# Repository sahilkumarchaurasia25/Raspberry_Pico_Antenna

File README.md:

# Raspberry_Pico_Antenna

You can refer the code from github repository by AndyRids, https://github.com/AndyRids/pico-nrf24 
Front view

Back View

Pcb design

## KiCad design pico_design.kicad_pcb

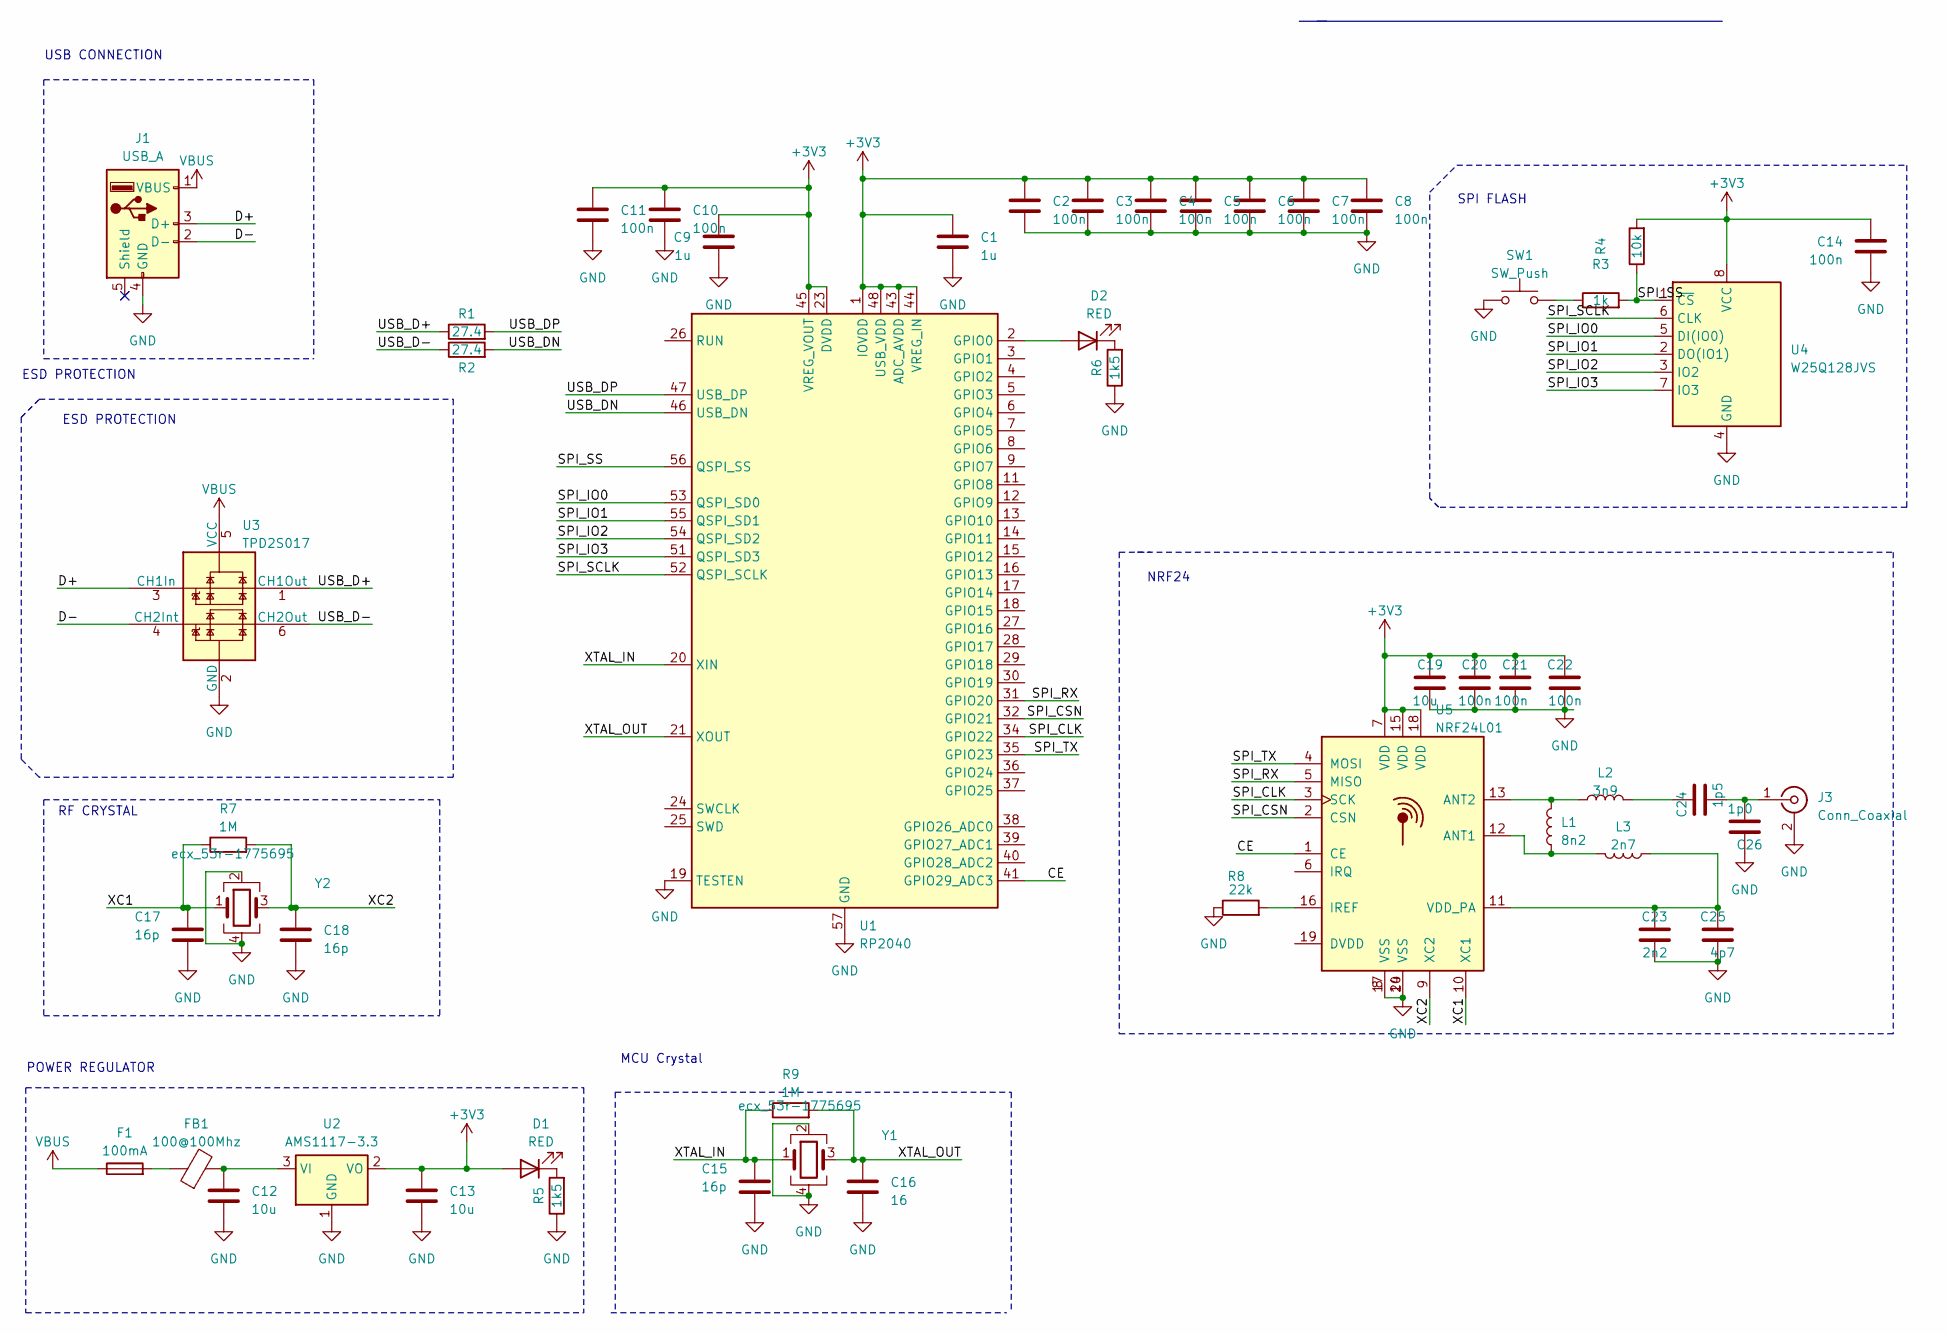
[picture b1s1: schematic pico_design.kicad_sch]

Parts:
C1, C9: 1u; C_0805_2012Metric
C2, C3, C4, C5, C6, C7, C8, C10, C11, C14, C20, C21, C22: 100n; C_0402_1005Metric
C12, C13, C19: 10u; C_0805_2012Metric
C15, C17, C18: 16p; C_0402_1005Metric
C16: 16; C_0402_1005Metric
C23: 2n2; C_0402_1005Metric
C24: 1p5; C_0402_1005Metric
C25: 4p7; C_0402_1005Metric
C26: 1p0; C_0402_1005Metric
D1, D2: RED; LED_0402_1005Metric
F1: 100mA; Fuse_0805_2012Metric
FB1: 100@100Mhz; C_0805_2012Metric
J1: USB_A; USB_A_CNCTech_1001-011-01101_Horizontal
J3: Conn_Coaxial; SMA_Samtec_SMA-J-P-X-ST-EM1_EdgeMount
L1: 8n2; L_0402_1005Metric
L2: 3n9; L_0402_1005Metric
L3: 2n7; L_0402_1005Metric
R1, R2: 27.4; R_0402_1005Metric
R3: 1k; R_0402_1005Metric
R4: 10k; R_0402_1005Metric
R5, R6: 1k5; R_0402_1005Metric
R7, R9: 1M; R_0402_1005Metric
R8: 22k; R_0402_1005Metric
SW1: SW_Push; SW_SPST_B3U-1000P
U1: RP2040; QFN-56-1EP_7x7mm_P0.4mm_EP3.2x3.2mm
U2: AMS1117-3.3; SOT-223-3_TabPin2
U3: TPD2S017; SOT-23-6
U4: W25Q128JVS; SOIC-8_5.23x5.23mm_P1.27mm
U5: NRF24L01; QFN-20-1EP_4x4mm_P0.5mm_EP2.5x2.5mm
Y1, Y2: ecx_53r-1775695; Crystal_SMD_SeikoEpson_TSX3225-4Pin_3.2x2.5mm

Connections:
+3V3: C1.1, C2.1, C3.1, C4.1, C5.1, C6.1, C7.1, C8.1, C9.1, C10.1, C11.1, C13.1, C14.1, C19.1, C20.1, C21.1, C22.1, D1.2 (A), R4.2, U1.1 (IOVDD), U1.10 (IOVDD), U1.22 (IOVDD), U1.23 (DVDD), U1.33 (IOVDD), U1.42 (IOVDD), U1.43 (ADC_AVDD), U1.44 (VREG_IN), U1.45 (VREG_VOUT), U1.48 (USB_VDD), U1.49 (IOVDD), U1.50 (DVDD), U2.2 (VO), U4.8 (VCC), U5.7 (VDD), U5.15 (VDD), U5.18 (VDD)
/CE: U1.41 (GPIO29_ADC3), U5.1 (CE)
/D+: J1.3 (D+), U3.3 (CH1In)
/D-: J1.2 (D-), U3.4 (CH2Int)
/SPI_CLK: U1.34 (GPIO22), U5.3 (SCK)
/SPI_CSN: U1.32 (GPIO21), U5.2 (CSN)
/SPI_IO0: U1.53 (QSPI_SD0), U4.5 (DI(IO0))
/SPI_IO1: U1.55 (QSPI_SD1), U4.2 (DO(IO1))
/SPI_IO2: U1.54 (QSPI_SD2), U4.3 (IO2)
/SPI_IO3: U1.51 (QSPI_SD3), U4.7 (IO3)
/SPI_RX: U1.31 (GPIO20), U5.5 (MISO)
/SPI_SCLK: U1.52 (QSPI_SCLK), U4.6 (CLK)
/SPI_SS: R3.2, R4.1, U1.56 (QSPI_SS), U4.1 (~CS)
/SPI_TX: U1.35 (GPIO23), U5.4 (MOSI)
/USB_D+: R1.1, U3.1 (CH1Out)
/USB_D-: R2.1, U3.6 (CH2Out)
/USB_DN: R2.2, U1.46 (USB_DN)
/USB_DP: R1.2, U1.47 (USB_DP)
/XC1: C17.1, R7.1, U5.10 (XC1), Y2.1
/XC2: C18.1, R7.2, U5.9 (XC2), Y2.3
/XTAL_IN: C15.1, R9.1, U1.20 (XIN), Y1.1
/XTAL_OUT: C16.1, R9.2, U1.21 (XOUT), Y1.3
GND: C1.2, C2.2, C3.2, C4.2, C5.2, C6.2, C7.2, C8.2, C9.2, C10.2, C11.2, C12.2, C13.2, C14.2, C15.2, C16.2, C17.2, C18.2, C19.2, C20.2, C21.2, C22.2, C23.2, C25.2, C26.1, J1.4 (GND), J3.2 (Ext), R5.1, R6.1, R8.1, SW1.1, U1.19 (TESTEN), U1.57 (GND), U2.1 (GND), U3.2 (GND), U4.4 (GND), U5.8 (VSS), U5.14 (VSS), U5.17 (VSS), U5.20 (VSS), Y1.2, Y1.4, Y2.2, Y2.4
unnamed: C24.1, L2.2
unnamed: D1.1 (K), R5.2
unnamed: D2.2 (A), U1.2 (GPIO0)
unnamed: D2.1 (K), R6.2
unnamed: F1.2, FB1.1
unnamed: C24.2, C26.2, J3.1 (In)
unnamed: R3.1, SW1.2
unnamed: C12.1, FB1.2, U2.3 (VI)
unnamed: L1.1, L3.2, U5.12 (ANT1)
unnamed: L1.2, L2.1, U5.13 (ANT2)
unnamed: R8.2, U5.16 (IREF)
unnamed: C23.1, C25.1, L3.1, U5.11 (VDD_PA)
VBUS: F1.1, J1.1 (VBUS), U3.5 (VCC)

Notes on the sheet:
POWER REGULATOR
NRF24
RF CRYSTAL
MCU Crystal
USB CONNECTION
ESD PROTECTION
ESD PROTECTION
SPI FLASH

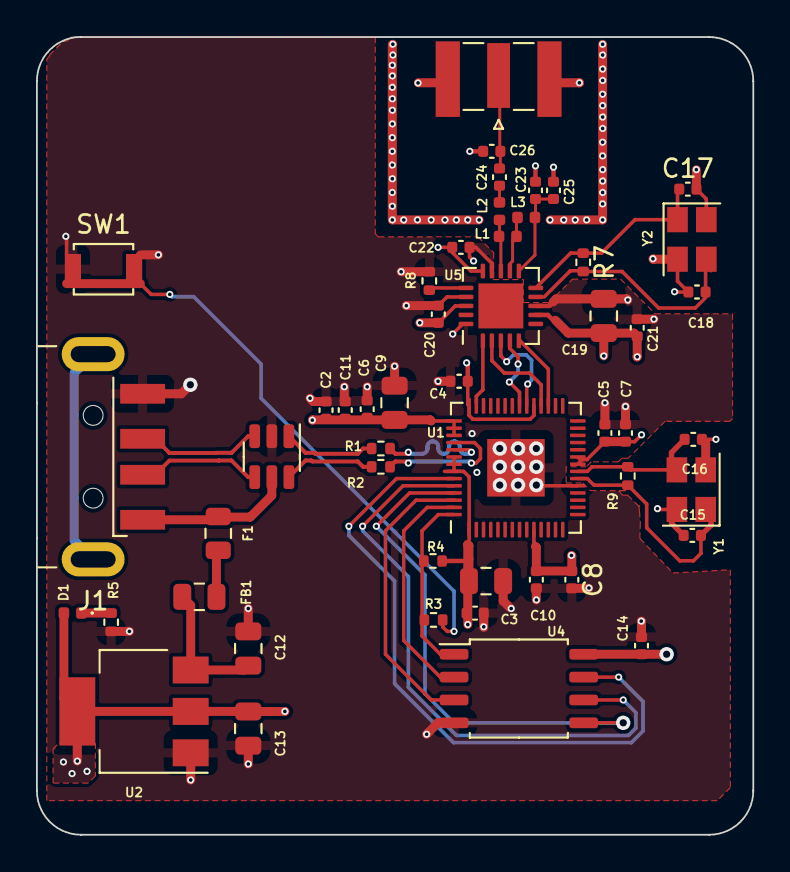
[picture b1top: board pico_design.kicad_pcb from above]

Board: 4 copper layers, 39.8 x 44.3 mm, 49 parts (0 on the bottom side), 34 nets.
